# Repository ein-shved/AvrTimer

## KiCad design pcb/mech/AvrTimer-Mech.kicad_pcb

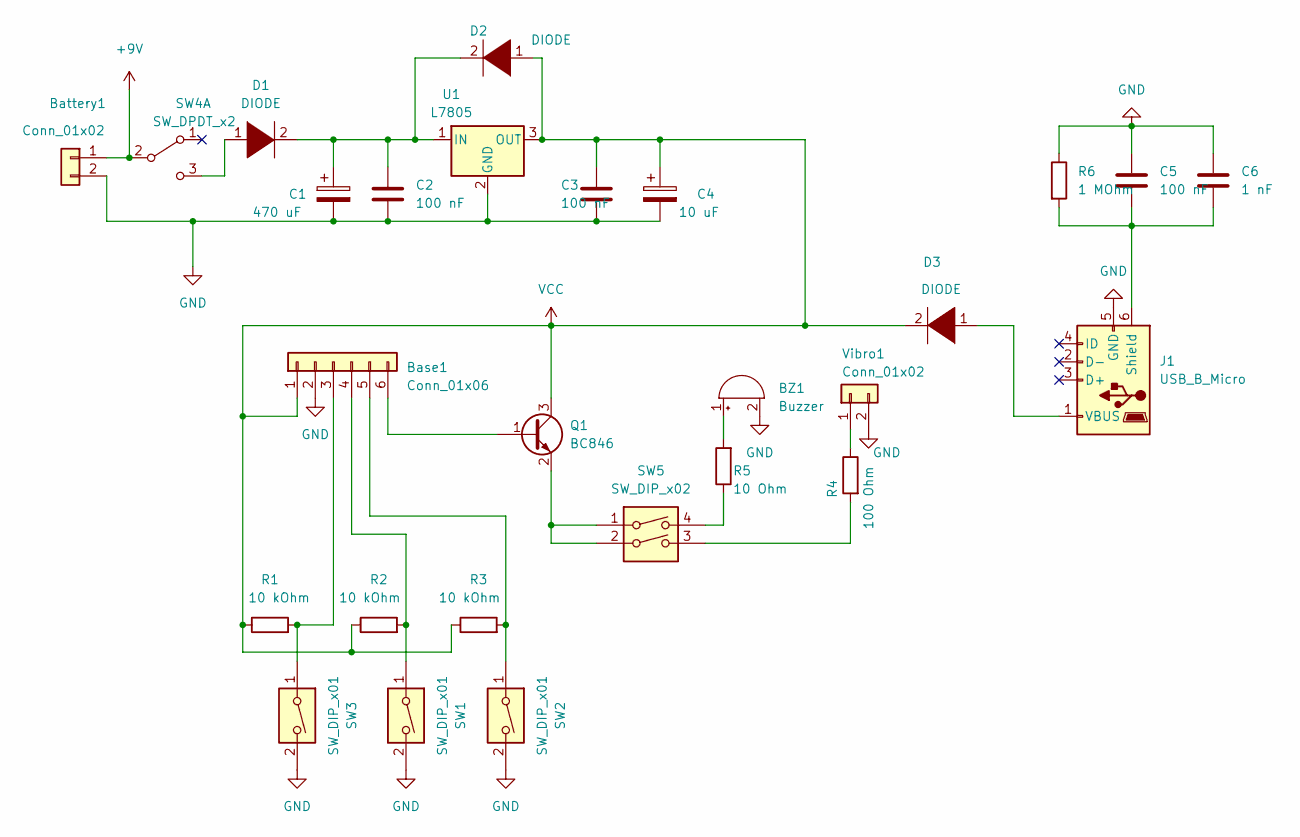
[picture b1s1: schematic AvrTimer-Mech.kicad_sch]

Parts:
BZ1: Buzzer; Buzzer_12x9.5RM7.6
Base1: Conn_01x06; JST_XH_B6B-XH-A_1x06_P2.50mm_Vertical
Battery1: Conn_01x02; JST_XH_B2B-XH-A_1x02_P2.50mm_Vertical
C1: 470 uF; CP_Radial_D10.0mm_P5.00mm
C2, C3, C5: 100 nF; C_0402_1005Metric_Pad0.74x0.62mm_HandSolder
C4: 10 uF; CP_Radial_D10.0mm_P5.00mm
C6: 1 nF; C_0402_1005Metric_Pad0.74x0.62mm_HandSolder
D1, D2, D3: DIODE; D_SOD-123F
J1: USB_B_Micro; USB_Micro-B_Molex_47346-0001
Q1: BC846; SOT-23
R1, R2, R3: 10 kOhm; R_1206_3216Metric_Pad1.30x1.75mm_HandSolder
R4: 100 Ohm; R_1206_3216Metric_Pad1.30x1.75mm_HandSolder
R5: 10 Ohm; R_1206_3216Metric_Pad1.30x1.75mm_HandSolder
R6: 1 MOhm; R_1206_3216Metric_Pad1.30x1.75mm_HandSolder
SW1: SW_DIP_x01; SW_PUSH-12mm
SW2, SW3: SW_DIP_x01; SW_PUSH_6mm
SW4: SW_DPDT_x2; L_KLS7_SS_12F19_G5
SW5: SW_DIP_x02; SW_DIP_SPSTx02_Slide_9.78x7.26mm_W7.62mm_P2.54mm
U1: L7805; TO-220-3_Horizontal_TabDown
Vibro1: Conn_01x02; JST_XH_B2B-XH-A_1x02_P2.50mm_Vertical

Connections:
+9V: Battery1.1, SW4.2 (B)
GND: BZ1.2 (+), Base1.2, Battery1.2, C1.2, C2.2, C3.2, C4.2, C5.1, C6.1, J1.5 (GND), R6.1, SW1.2, SW2.2, SW3.2, U1.2 (GND), Vibro1.2
unnamed: BZ1.1 (-), R5.2
unnamed: Base1.3, R1.2, SW3.1
unnamed: Base1.4, R2.2, SW1.1
unnamed: Base1.5, R3.2, SW2.1
unnamed: Base1.6, Q1.1 (B)
unnamed: C1.1, C2.1, D1.2 (A), D2.2 (A), U1.1 (IN)
unnamed: C5.2, C6.2, J1.6 (Shield), R6.2
unnamed: D1.1 (K), SW4.3 (C)
unnamed: D3.1 (K), J1.1 (VBUS)
unnamed: Q1.2 (E), SW5.1, SW5.2
unnamed: R4.1, Vibro1.1
unnamed: R4.2, SW5.3
unnamed: R5.1, SW5.4
VCC: Base1.1, C3.1, C4.1, D2.1 (K), D3.2 (A), Q1.3 (C), R1.1, R2.1, R3.1, U1.3 (OUT)

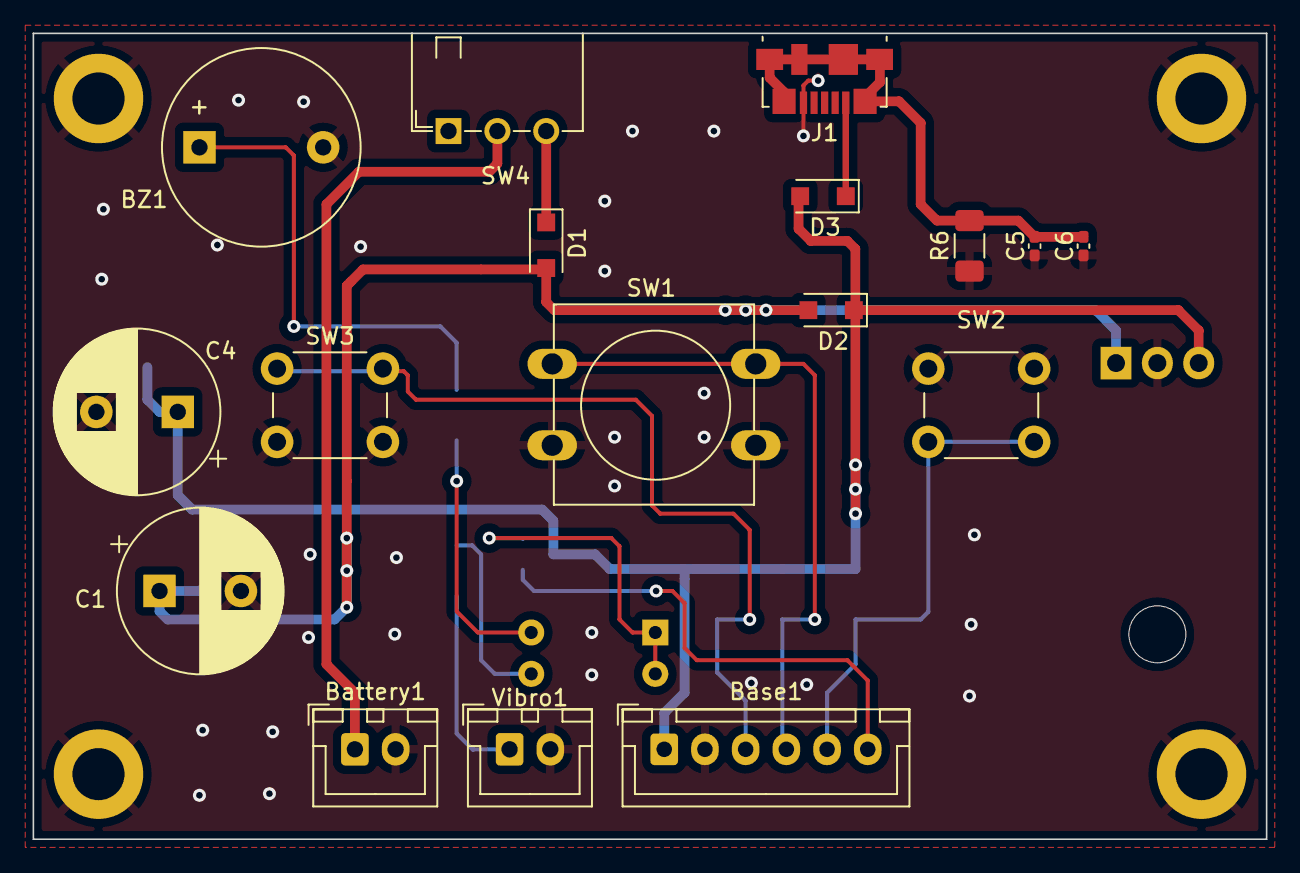
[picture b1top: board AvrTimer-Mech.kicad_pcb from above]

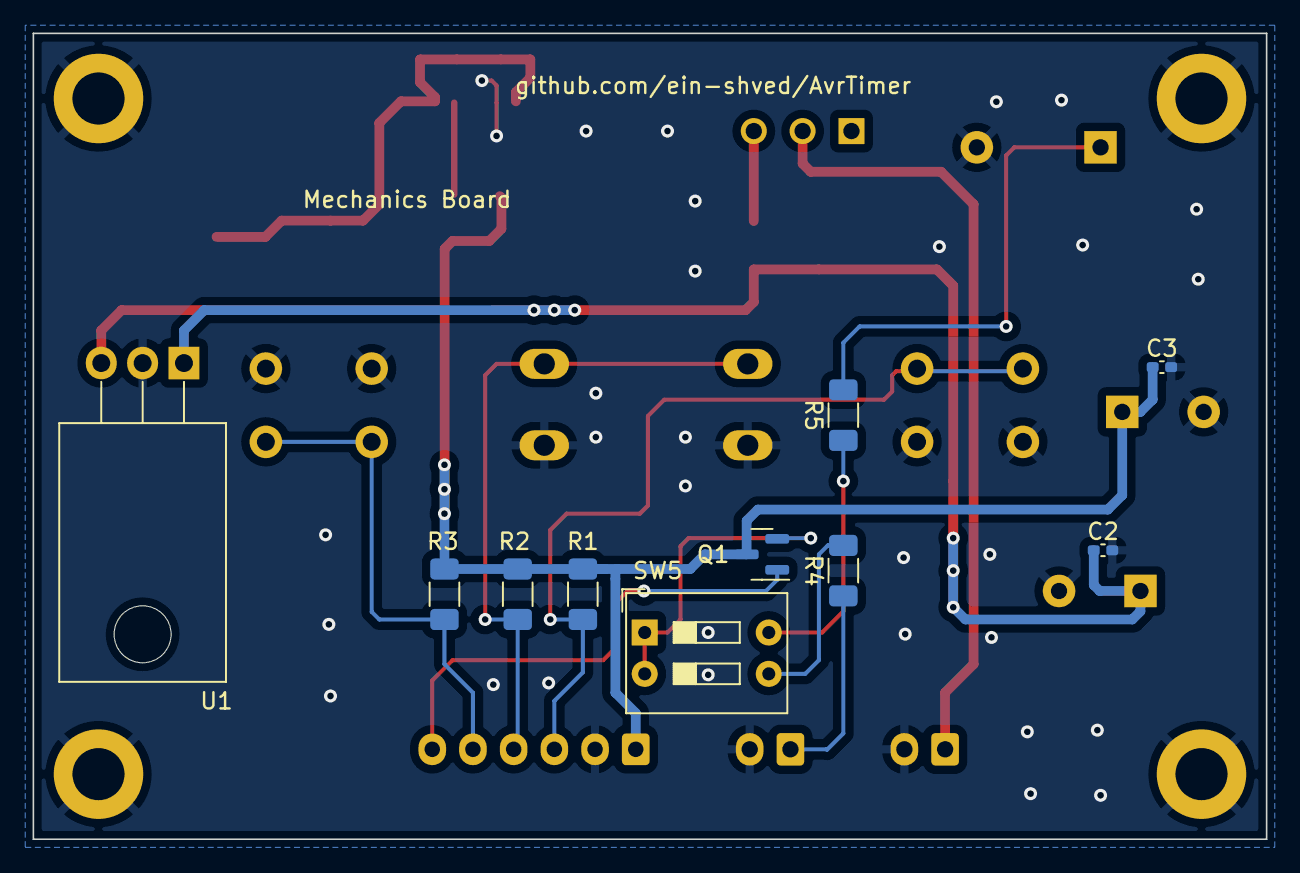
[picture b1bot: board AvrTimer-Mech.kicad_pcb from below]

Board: 2 copper layers, 75.8 x 49.5 mm, 27 parts (10 on the bottom side), 16 nets.

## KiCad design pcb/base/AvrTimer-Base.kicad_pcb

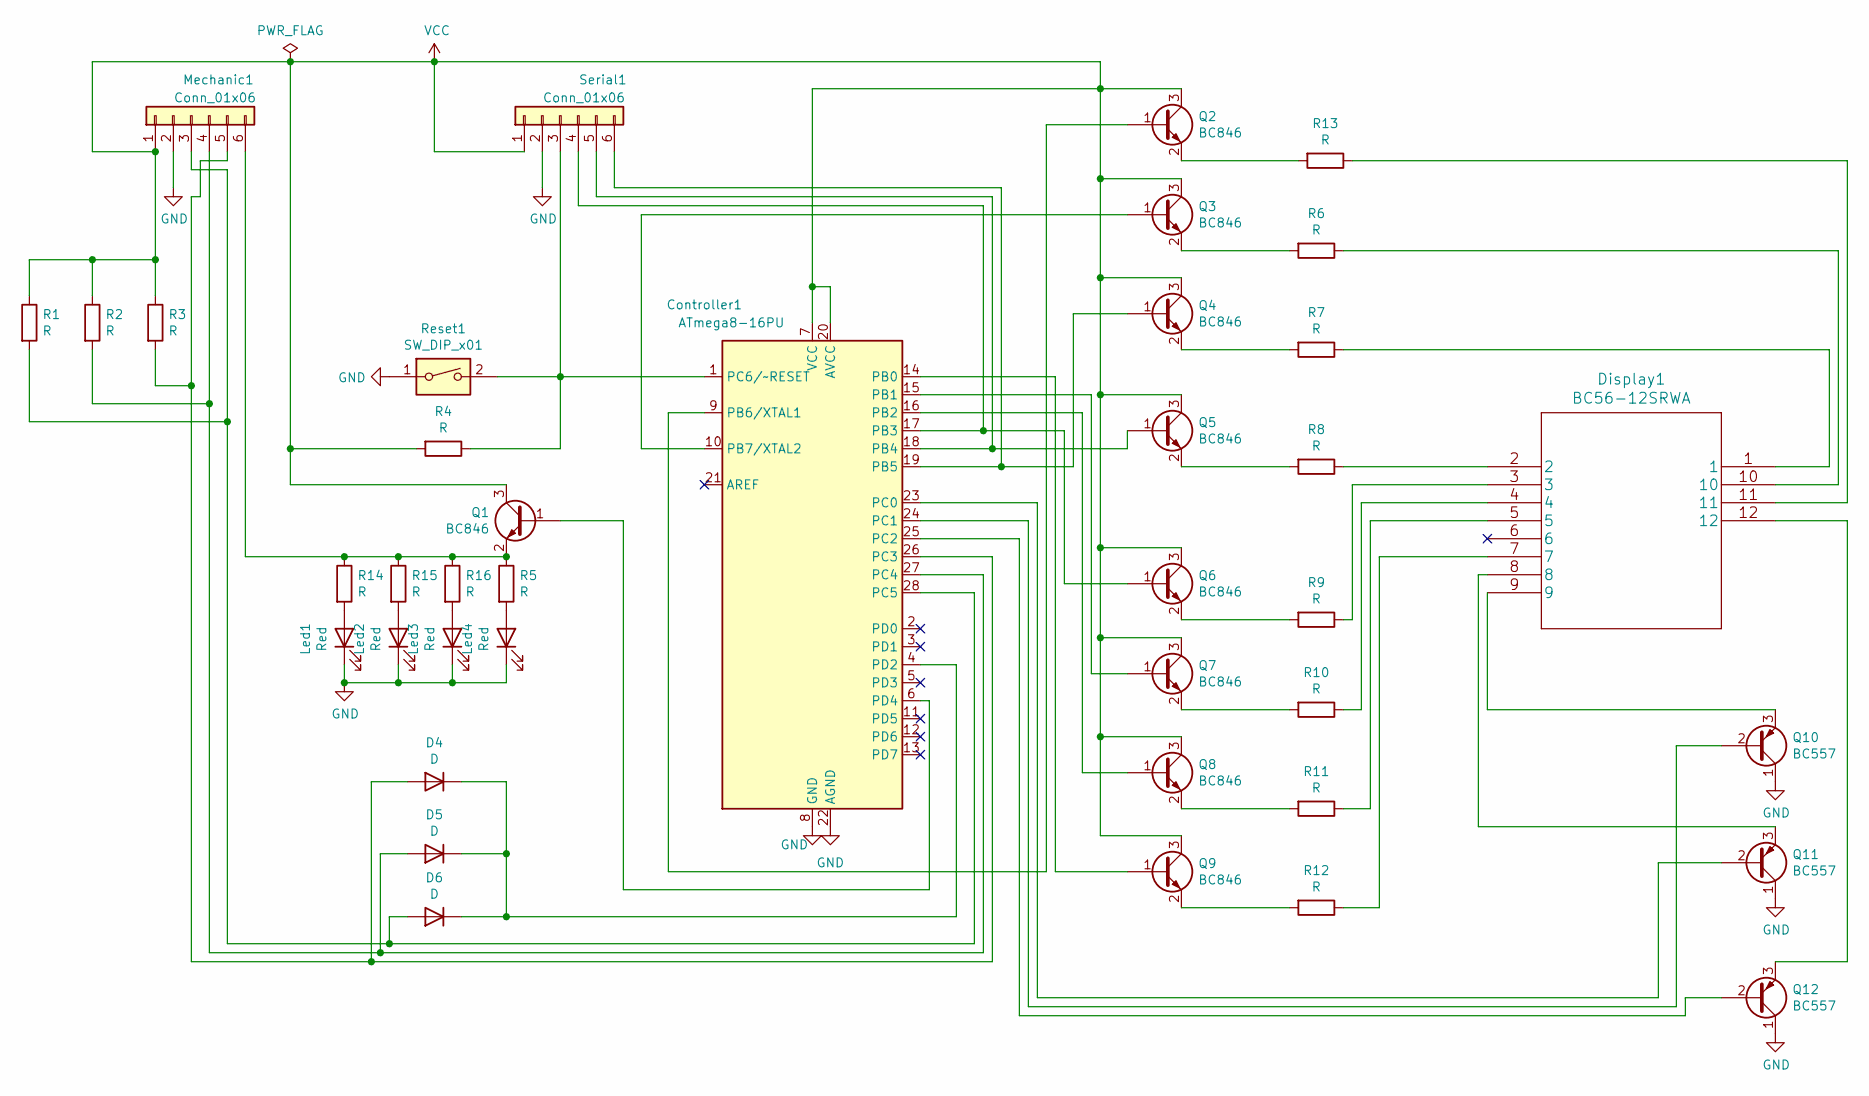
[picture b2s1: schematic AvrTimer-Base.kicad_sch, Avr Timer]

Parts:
Controller1: ATmega8-16PU; DIP-28_W7.62mm
D4, D5, D6: D; D_SOD-123F
Display1: BC56-12SRWA; BC56-12GWA
Led1, Led2, Led3, Led4: Red; LED_1210_3225Metric_Pad1.42x2.65mm_HandSolder
Mechanic1: Conn_01x06; JST_XH_B6B-XH-A_1x06_P2.50mm_Vertical
Q1, Q2, Q3, Q4, Q5, Q6, Q7, Q8, Q9: BC846; SOT-23_Handsoldering
Q10, Q11, Q12: BC557; SOT-23_Handsoldering
R1, R2, R3, R4, R5, R6, R7, R8, R9, R10, R11, R12, R13, R14, R15, R16: R; R_1206_3216Metric_Pad1.30x1.75mm_HandSolder
Reset1: SW_DIP_x01; SW_PUSH_6mm
Serial1: Conn_01x06; PinHeader_1x06_P2.54mm_Vertical

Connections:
GND: Controller1.8 (GND), Controller1.22 (AGND), Led1.1 (K), Led2.1 (K), Led3.1 (K), Led4.1 (K), Mechanic1.2, Q10.1 (C), Q11.1 (C), Q12.1 (C), Reset1.1, Serial1.2
unnamed: Controller1.1 (PC6/~RESET), R4.1, Reset1.2, Serial1.3
unnamed: Controller1.4 (PD2), D4.1 (K), D5.1 (K), D6.1 (K)
unnamed: Controller1.6 (PD4), Q1.1 (B)
unnamed: Controller1.9 (PB6/XTAL1), Q2.1 (B)
unnamed: Controller1.10 (PB7/XTAL2), Q3.1 (B)
unnamed: Controller1.14 (PB0), Q9.1 (B)
unnamed: Controller1.15 (PB1), Q7.1 (B)
unnamed: Controller1.16 (PB2), Q8.1 (B)
unnamed: Controller1.17 (PB3), Q6.1 (B), Serial1.4
unnamed: Controller1.18 (PB4), Q5.1 (B), Serial1.5
unnamed: Controller1.19 (PB5), Q4.1 (B), Serial1.6
unnamed: Controller1.23 (PC0), Q11.2 (B)
unnamed: Controller1.24 (PC1), Q10.2 (B)
unnamed: Controller1.25 (PC2), Q12.2 (B)
unnamed: Controller1.26 (PC3), D4.2 (A), Mechanic1.5, R3.2
unnamed: Controller1.27 (PC4), D5.2 (A), Mechanic1.4, R2.2
unnamed: Controller1.28 (PC5), D6.2 (A), Mechanic1.3, R1.2
unnamed: Display1.1, R7.1
unnamed: Display1.2, R8.1
unnamed: Display1.3, R9.1
unnamed: Display1.4, R10.1
unnamed: Display1.5, R11.1
unnamed: Display1.7, R12.1
unnamed: Display1.8, Q11.3 (E)
unnamed: Display1.9, Q10.3 (E)
unnamed: Display1.10, R6.1
unnamed: Display1.11, R13.1
unnamed: Display1.12, Q12.3 (E)
unnamed: Led1.2 (A), R14.2
unnamed: Led2.2 (A), R15.2
unnamed: Led3.2 (A), R16.2
unnamed: Led4.2 (A), R5.2
unnamed: Mechanic1.6, Q1.2 (E), R5.1, R14.1, R15.1, R16.1
unnamed: Q2.2 (E), R13.2
unnamed: Q3.2 (E), R6.2
unnamed: Q4.2 (E), R7.2
unnamed: Q5.2 (E), R8.2
unnamed: Q6.2 (E), R9.2
unnamed: Q7.2 (E), R10.2
unnamed: Q8.2 (E), R11.2
unnamed: Q9.2 (E), R12.2
VCC: Controller1.7 (VCC), Controller1.20 (AVCC), Mechanic1.1, Q1.3 (C), Q2.3 (C), Q3.3 (C), Q4.3 (C), Q5.3 (C), Q6.3 (C), Q7.3 (C), Q8.3 (C), Q9.3 (C), R1.1, R2.1, R3.1, R4.2, Serial1.1

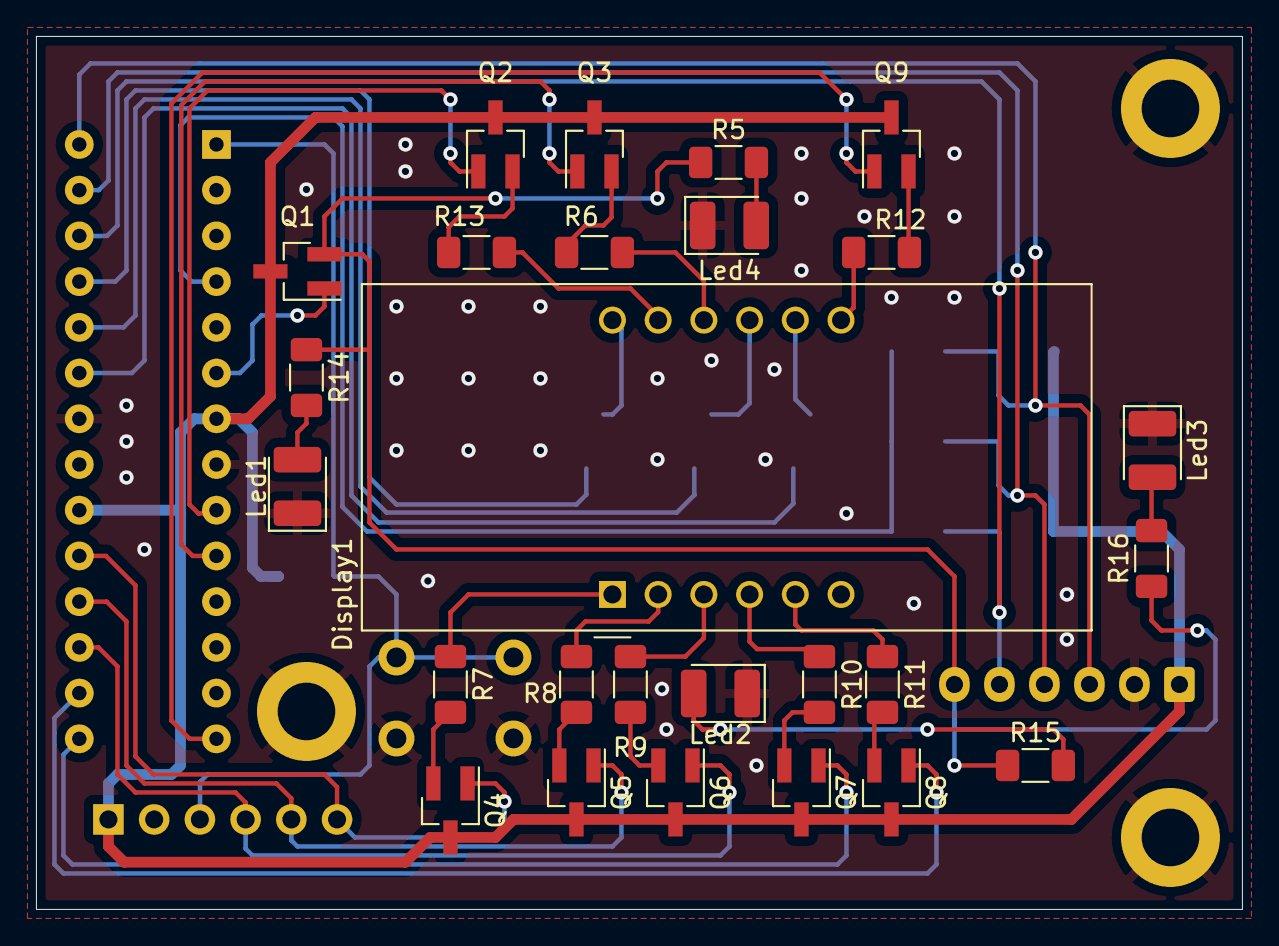
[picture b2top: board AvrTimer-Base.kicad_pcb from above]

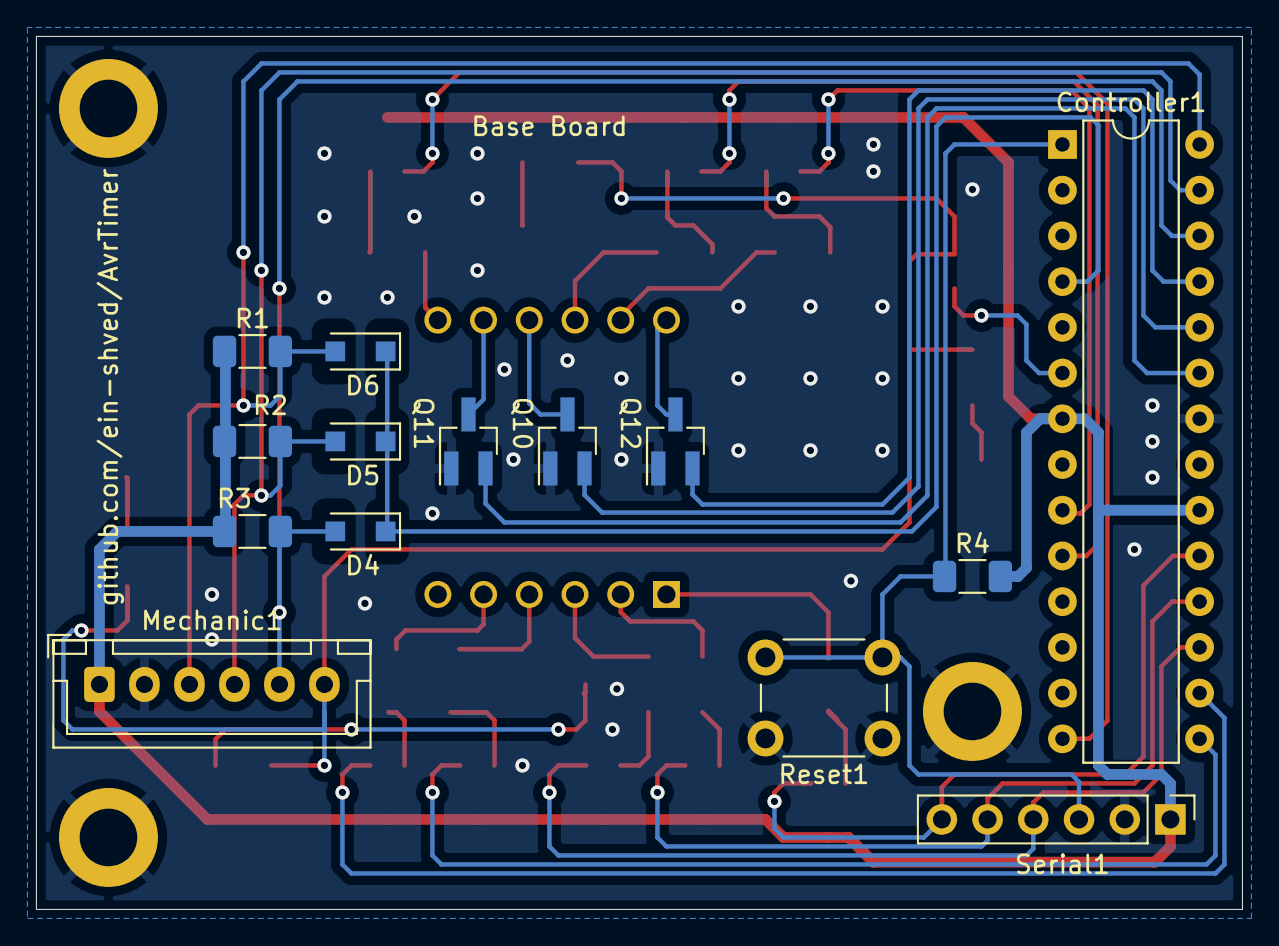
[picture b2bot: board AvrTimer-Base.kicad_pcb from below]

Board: 2 copper layers, 67.0 x 48.5 mm, 40 parts (14 on the bottom side), 43 nets.

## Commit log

2022-03-20 Initial commit
    This commit should be spited, but sorry.
    Here is:
    * Fsm, which handles ticking and configuring timer.
    * Printer, which direly controls display with 3 seven-segment digits.
    * Program buttons debouncing
    * Saving config to eeprom
2022-04-14 Working firmware
2022-04-14 Add scheme and pcb for base board
2022-04-16 Partly update scheme for hand-soldering
2022-04-16 Update all footprints to correct ones
2022-04-19 Update after Alexander's Y. review
2022-04-21 Final version of base board
2022-04-21 Split project to subfolders
2022-04-24 Add local pretty library
    Add source reference and board name o Base board
2022-04-24 Implement mechanics scheme and board
2022-04-24 Replace diode footprints to shop real ones
2022-04-26 Update after Alexander's review
2022-06-04 [PCB] Add values for R and C
2022-06-04 Fix segments placements for onboard setup
    Add special SEGMENT_X macro for handy digits definition
    Implement segments probe mode
    Fix hiding number
    Fix buttons and segments pins
2022-06-04 Update default values
2022-10-24 Some fixes in printer with number hiding
2022-10-24 [body] Add *stl and *step files for body printing
